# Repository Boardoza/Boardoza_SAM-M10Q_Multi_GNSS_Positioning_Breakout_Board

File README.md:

# Boardoza SAM-M10Q GNSS Breakout Board

The **Boardoza SAM-M10Q GNSS Breakout Board** is a high-performance global navigation satellite system (GNSS) solution based on the **u-blox SAM-M10Q** module. Featuring an integrated patch antenna, SAW filter, and LNA (Low Noise Amplifier), this board delivers exceptional sensitivity, fast acquisition time, and robust interference immunity for reliable positioning.

Built on the **u-blox M10 standard precision GNSS platform**, the SAM-M10Q supports concurrent reception of **GPS, GLONASS, Galileo, and BeiDou** signals. With multi-constellation support and advanced anti-jamming and anti-spoofing detection, this breakout board is ideal for applications such as asset tracking, drone navigation, smart agriculture, robotics, fleet management, wearable tracking devices, and IoT positioning systems.

## [Click here to purchase!](https://www.ozdisan.com/ureticiler/boardoza)

| Front Side | Back Side |
|:---:|:---:|
|  |  |

---

## Key Features

- **Multi-GNSS Support:** Concurrent reception of GPS, GLONASS, Galileo, and BeiDou signals.
- **Integrated Patch Antenna:** Built-in antenna design for compact and simplified integration.
- **High Sensitivity Reception:** Excellent satellite acquisition even in weak signal environments.
- **Advanced Jamming & Spoofing Detection:** Reports interference attempts directly to the host MCU.
- **Flexible Communication:** Supports both **UART** and **I²C** interfaces.    
- **Wide Input Voltage Range:** Operates with both **3.3V and 5V** systems.

---

## Technical Specifications

**Model:** u-blox SAM-M10Q  
**Manufacturer:** Boardoza     
**Manufacturer IC:** u-blox AG  
**GNSS Platform:** u-blox M10  
**Input Voltage:** 3.3V – 5.5V  
**Power Input Type:** 4-pin 2.50mm header  
**Voltage Logic Level:** 3.3V (PPS, RST, INT, SAFE pins), other pins are both compitable with 3.3 and 5V      
**Communication Interfaces:** UART, I²C   
**Concurrent GNSS:** GPS, GLONASS, Galileo, BeiDou  
**Integrated Components:** Patch Antenna, SAW Filter, LNA  
**Position Accuracy:** ~1.5 m CEP (typical, open sky)  
**Cold Start Time:** ~23 s (typical)  
**Hot Start Time:** ~1 s (typical)  
**Operating Temperature:** -40°C to +85°C  
**Board Dimensions:** 40mm x 40mm   

---

## Board Pinout

### ( J1 ) UART Connector

| Pin Number | Pin Name | Description |
|:---:|:---:|---|
| 1 | VCC | Power Supply (3.3V – 5.5V) |
| 2 | RXD | UART Receive Data |
| 3 | TXD | UART Transmit Data |
| 4 | GND | Ground |

---

### ( J2 ) I²C Connector

| Pin Number | Pin Name | Description |
|:---:|:---:|---|
| 1 | VCC | Power Supply (3.3V – 5.5V) |
| 2 | SCL | I²C Serial Clock |
| 3 | SDA | I²C Serial Data |
| 4 | GND | Ground |

---

### ( J3 ) Control & Timing Pins

| Pin Number | Pin Name | Description |
|:---:|:---:|---|
| 1 | PPS (TIMEPULSE) | Precision timing output (PIO4, 2 mA drive capability) |
| 2 | RST | System Reset (Active Low, ≥1 ms pulse) |
| 3 | INT | External Interrupt Input |
| 4 | SAFE | Safeboot Mode (Active Low, leave open if unused) |

---

## Board Dimensions

---

## Step Files

[Boardoza SAM-M10Q.step](./assets/UBLOX_SAM_M10Q%20Step.step)

---

## Datasheet

[SAM-M10Q Datasheet (UBX-22013293)](./assets/UBLOX_SAM_M10Q%20Datasheet.pdf)

---

## Version History

- V1.0.0 - Initial Release

---

## Support

- If you have any questions or need support, please contact **support@boardoza.com**

---

## **License**

This repository contains both hardware and software components:

### **Hardware Design**

[![CC BY-SA 4.0][cc-by-sa-shield]][cc-by-sa]

All hardware design files are licensed under [Creative Commons Attribution-ShareAlike 4.0 International License][cc-by-sa].

[cc-by-sa]: http://creativecommons.org/licenses/by-sa/4.0/
[cc-by-sa-shield]: https://img.shields.io/badge/License-CC%20BY--SA%204.0-lightgrey.svg

### **Software/Firmware**

[![BSD-3-Clause][bsd-shield]][bsd]

All software and firmware are licensed under [BSD 3-Clause License][bsd].

[bsd]: https://opensource.org/licenses/BSD-3-Clause
[bsd-shield]: https://img.shields.io/badge/License-BSD%203--Clause-blue.svg

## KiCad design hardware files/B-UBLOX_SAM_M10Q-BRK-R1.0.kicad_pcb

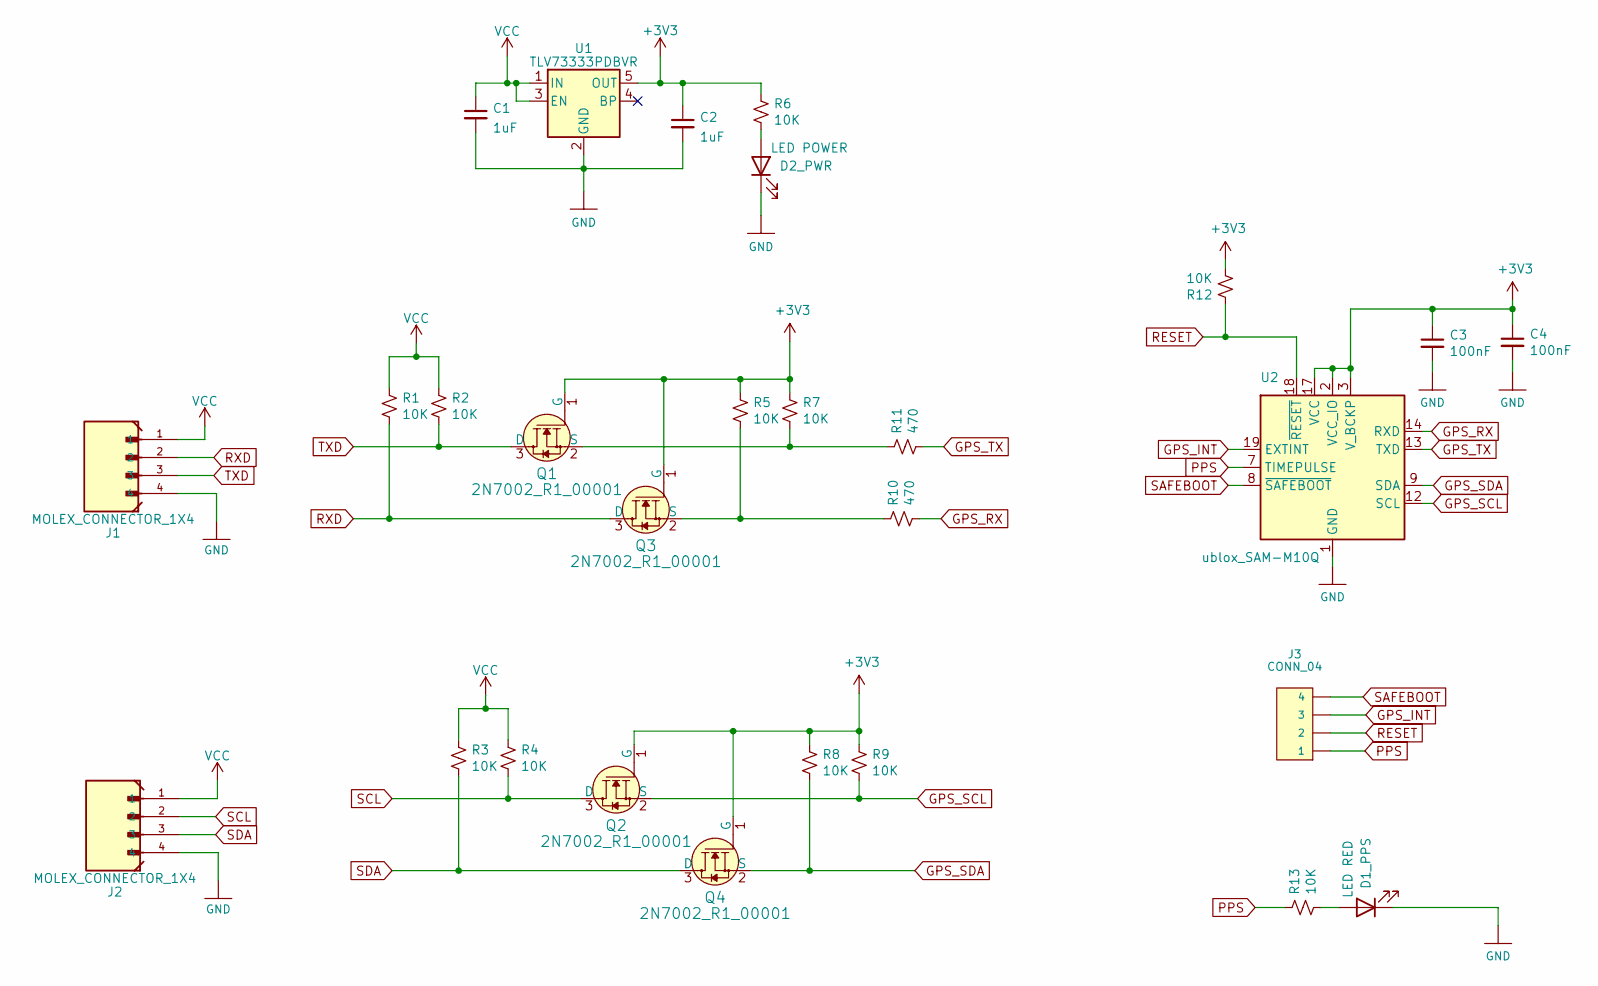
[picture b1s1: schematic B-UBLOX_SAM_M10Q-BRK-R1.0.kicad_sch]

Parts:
C1, C2: 1uF; C_0603_1608Metric
C3, C4: 100nF; C_0603_1608Metric
D1_PPS: LED RED; LED_0603_1608Metric
D2_PWR: LED POWER; LED_0603_1608Metric
J1, J2: MOLEX_CONNECTOR_1X4; 2317-04S_1x04_P2.50mm_Vertical; PARTREV A
J3: CONN_04; 1X04
Q1, Q2, Q3, Q4: 2N7002_R1_00001; SOT-23-3; MPN 2N7002-7-F; Digi-Key_PN 2N7002-FDICT-ND
R1, R2, R3, R4, R5, R6, R7, R8, R9, R12, R13: 10K; R_0603_1608Metric
R10, R11: 470; R_0603_1608Metric
U1: TLV73333PDBVR; SOT-23-5
U2: ublox_SAM-M10Q; ublox_SAM-M8Q

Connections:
+3V3: C2.1, C3.1, C4.1, Q1.1 (G), Q2.1 (G), Q3.1 (G), Q4.1 (G), R5.1, R6.1, R7.1, R8.1, R9.1, R12.2, U1.5 (OUT), U2.2 (VCC_IO), U2.3 (V_BCKP), U2.17 (VCC)
GND: C1.2, C2.2, C3.2, C4.2, J1.4, J2.4, U1.2 (GND), U2.1 (GND), U2.4 (GND), U2.5 (GND), U2.6 (GND), U2.10 (GND), U2.11 (GND), U2.15 (GND), U2.16 (GND), U2.20 (GND); also elsewhere on the board
GPS_INT: J3.3, U2.19 (EXTINT)
GPS_RX: R10.2, U2.14 (RXD)
GPS_SCL: Q2.2 (S), R9.2, U2.12 (SCL)
GPS_SDA: Q4.2 (S), R8.2, U2.9 (SDA)
GPS_TX: R11.2, U2.13 (TXD)
unnamed 7: R13.2; also elsewhere on the board
unnamed 8: D2_PWR.2 (A), R6.2; also elsewhere on the board
unnamed: Q1.2 (S), R7.2, R11.1
unnamed: Q3.2 (S), R5.2, R10.1
PPS: J3.1, R13.1, U2.7 (TIMEPULSE)
RESET: J3.2, R12.1, U2.18 (~RESET)
RXD: J1.2, Q3.3 (D), R1.2
SAFEBOOT: J3.4, U2.8 (~SAFEBOOT)
SCL: J2.2, Q2.3 (D), R4.2
SDA: J2.3, Q4.3 (D), R3.2
TXD: J1.3, Q1.3 (D), R2.2
VCC: C1.1, J1.1, J2.1, R1.1, R2.1, R3.1, R4.1, U1.1 (IN), U1.3 (EN)

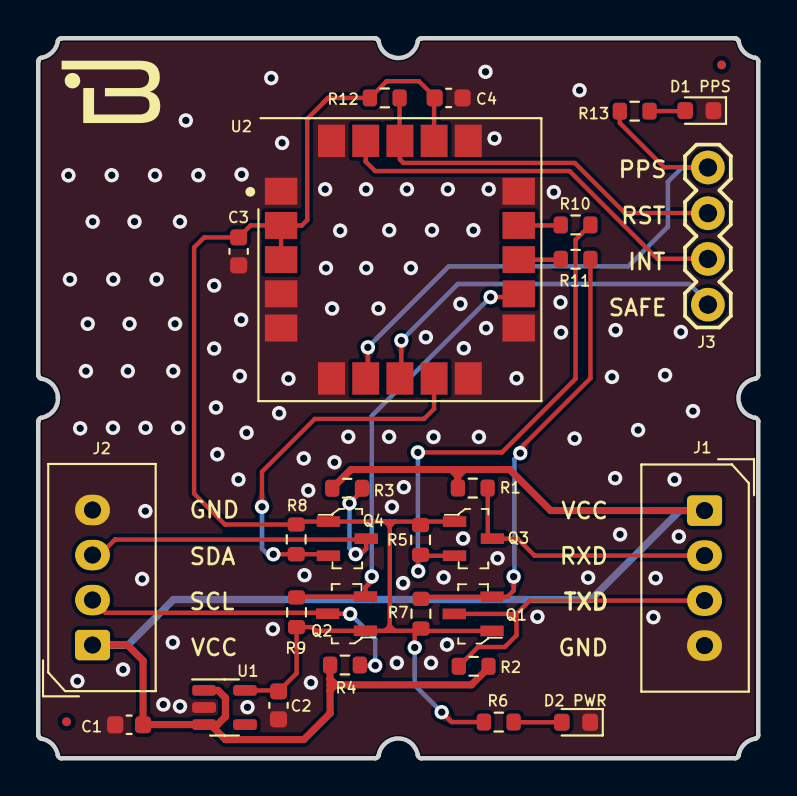
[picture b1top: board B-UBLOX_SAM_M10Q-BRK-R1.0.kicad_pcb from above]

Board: 2 copper layers, 40.0 x 40.0 mm, 28 parts (0 on the bottom side), 19 nets.

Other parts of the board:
D1 PPS: LED RED; LED_0603_1608Metric
D2 PWR: LED POWER; LED_0603_1608Metric

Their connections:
GND: D1 PPS.1 (K), D2 PWR.1 (K); also elsewhere on the board
unnamed 7: D1 PPS.2 (A); also elsewhere on the board
unnamed 8: D2 PWR.2 (A); also elsewhere on the board
